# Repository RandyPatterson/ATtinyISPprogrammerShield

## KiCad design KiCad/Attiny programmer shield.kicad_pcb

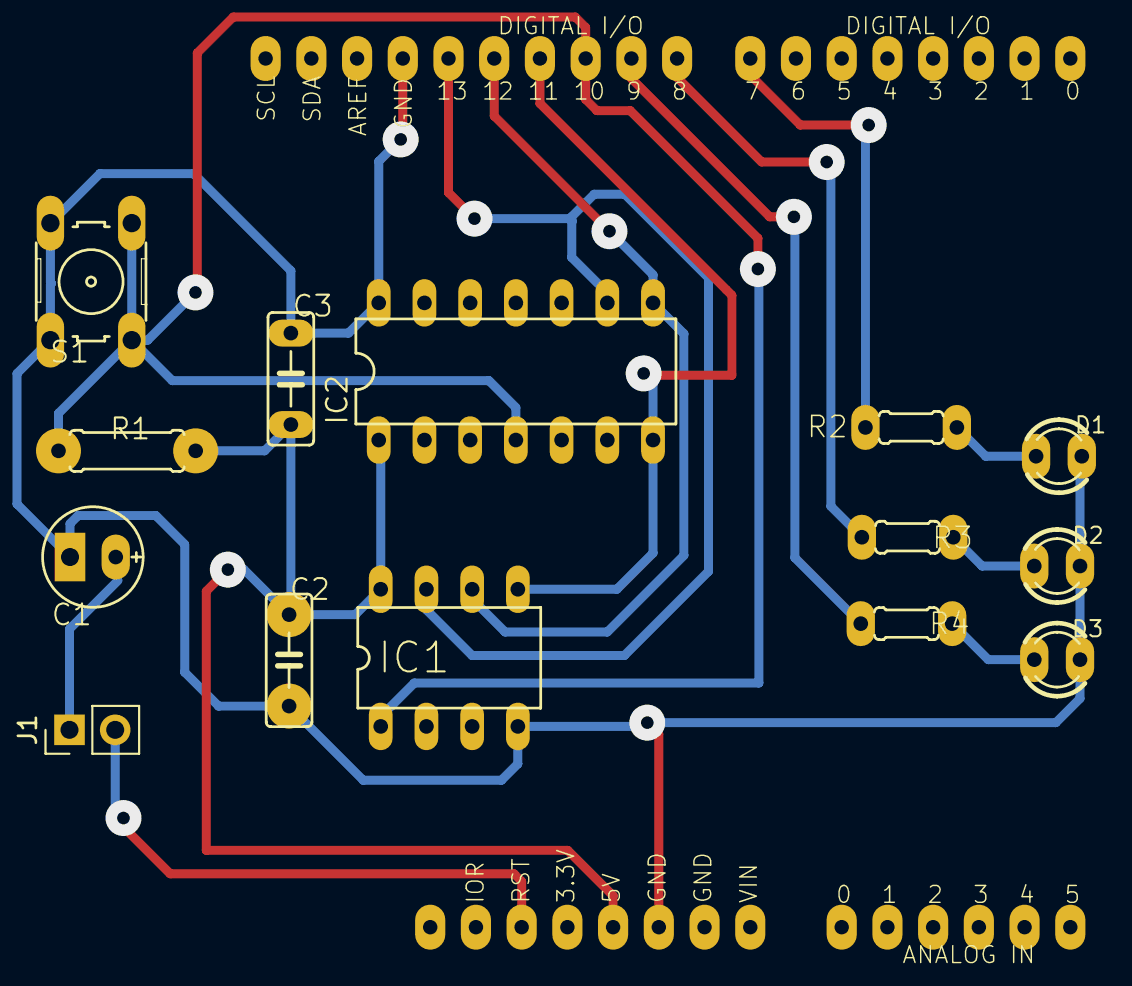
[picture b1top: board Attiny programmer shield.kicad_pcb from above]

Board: 2 copper layers, 15 parts (0 on the bottom side), 14 nets.

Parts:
C1: 10µF/16V; E2,5-6E
C2, C3: 100nF; C050-025X075
D1: Yellow - programming; LED3MM
D2: Red - error; LED3MM
D3: Green - ISP running; LED3MM
IC1: attiny10/11/12/13/15/22/25/45/85; DIL08
IC2: attiny24/44/84; DIL14
J1: Conn_01x02_Male; PinHeader_1x02_P2.54mm_Vertical
R1: 10k; 0207_7
R2, R3, R4: 270; 0204_5
S1: Reset; B3F-10XX
U$1: Arduino Uno; ARDUINO-R3

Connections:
+UB: C2.2, C3.2, IC1.8 (VCC), IC2.1 (VCC), R1.2, U$1.5V
/MISO: IC1.6 ((MISO)PB1), IC2.8 ((PCINT5/OC1B/MISO/DO/ADC5)PA5), U$1.D12
/MOSI: IC1.5 ((MOSI)PB0), IC2.7 ((PCINT6/OC1A/SDA/MOSI/ADC6)PA6), U$1.D11
/RESET: IC1.1 ((RESET)PB5), IC2.4 ((PCINT11/RESET/DW)PB3), R1.1, S1.1 (S), S1.2 (S1), U$1.D10
/SCK: IC1.7 ((SCK)PB2), IC2.9 ((PCINT4/T1/SCL/USCK/ADC4)PA4), U$1.D13
GND: C1.-, C2.1, C3.1, D1.K (C), D2.K (C), D3.K (C), IC1.4 (GND), IC2.14 (GND), S1.3, S1.4 (P1), U$1.GND, U$1.GND1, U$1.GND2
unnamed: C1.+, J1.1
unnamed: D1.A, R2.2
unnamed: D2.A, R3.2
unnamed: D3.A, R4.2
unnamed: R2.1, U$1.D7
unnamed: R3.1, U$1.D8
unnamed: R4.1, U$1.D9
unnamed: J1.2, U$1.RESET

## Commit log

2022-12-13 Added KiCad conversion and FlatCAM project
